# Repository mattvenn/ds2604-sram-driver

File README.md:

# pinball high scores

Reading the high scores out of the SRAM of a pinball machine.

[inspiration](http://spritesmods.com/?art=twitter1943)

[Tweet thread
documentation](https://threadreaderapp.com/thread/1040240733838557184.html)

After modelling, testing and reading/writing to the SRAM. I only needed to
listen to the bus lines to know when the data was being read. That is done by
[addr_listener](hdl/addr_listener):

    always @(clk) begin
        if(sram_ce) begin
            if(ce_counter < WAIT)
                ce_counter <= ce_counter + 1;
            else if(ce_counter == WAIT) begin
                case(sram_address)
                    sc_100_k:
                        high_score[23:20] <= sram_data_pins[3:0];
                    sc_10_k:
                        high_score[19:16] <= sram_data_pins[3:0];
                    sc_1_k:
                        high_score[15:12] <= sram_data_pins[3:0];
                    sc_100:
                        high_score[11: 8] <= sram_data_pins[3:0];
                    sc_10:
                        high_score[ 7: 4] <= sram_data_pins[3:0];
                    sc_1:
                        high_score[ 3: 0] <= sram_data_pins[3:0];
                endcase
            end
        else
            ce_counter <= 0;
        end 
    end

## plan

* the ds2064 is socketed, so make a [breakout board](ram-fpga) that passes through the connections. 
* add an FPGA that can listen to the 13 address lines, the 8 data lines and the 3 read/write/select pins = 24pins.
* when in write mode, with address in the high score range the FPGA reads the data off the bus.
* write [ds2064 driver](hdl/sram_driver/README.md)

## board test

* data pins tx - ok
* data pins rx - ok - very high impedance!
* addr pins tx - ok
* addr pins rx - ok
* ctrl pins rx - ok
* ctrl pins tx - ok
* on programming fpga, 5v line draws up to 40mA
* added 10k resistor from tranceiver !oe to FPGA 3.3v to keep them off while being programmed

## functional test

* read and write work separately with python control
* however, a write followed by a read works with ram non connected!

# Resources

http://www.pinballsupernova.com/Williams%20Repair%20Guide/Williams%201990-1999%20WPC.pdf
page 20 ram details

emulator https://github.com/neophob/wpc-emu
http://bcd.github.io/freewpc/The-WPC-Hardware.html#The-WPC-Hardware

The CPU board contains the main processor: a Motorola 68B09E, running at 2Mhz. It is an 8-bit/16-bit CPU with a 64KB address space. Bank switching is required to address more than 64KB. On reset, location 0xFFFE is read to determine the address of the first instruction.

8KB of RAM is located at physical address 0x0000. When power is turned off, three AA batteries on the CPU board maintain the state of the RAM. 

## WPC89

fairly sure this is the main board on my doctor who pinball.
[good overview here](http://level42.ca/files/PinRepair/System%20WPC/WPC%20part1/index1.htm)

It uses a battery backed up [ds2064](docs/ds2064.pdf) to store audits and score I hope.

[Schematic](docs/wpc89.pdf)

# Available machines to try

## bride

https://www.ipdb.org/machine.cgi?gid=1502
williams wpc

## high speed

https://www.ipdb.org/machine.cgi?id=1176
Williams System 11

## grand lizard

https://www.ipdb.org/machine.cgi?id=1070
williams system 11

## fire power 

https://www.ipdb.org/machine.cgi?id=856
williams system 6  (rottendog MPU327-4)
good photo: https://pinside.com/pinball/market/classifieds/archive/25465

rottendog sram chip:
https://www.mouser.es/datasheet/2/12/AS6C6264A-1288481.pdf

initial high score is 550,000 = 0x00_g08_64_70 

couldn't find it, so got a fake new score: 803950 = 0x0c_44_6e
         = 80 39 50

         = 50 39 50

motorola 6800 is big endian, intel is little endian

After searching for packed BCD of default string - got a match at 0x1149

    grep -A3 '^1149' dump.8192.5
    1149 55
    114a 00
    114b 00
    114c 00

Then checked for the new high score that we set 803950:

    grep -A3 '^1149' dump.8000.newhigh
    1149 80
    114a 03
    114b 39
    114c 05

Write this to a default chip:

    ./control.py --port /dev/ttyUSB1 --addr-start 1149 --addr-end 114d --read --hex
    1149 80
    114a 03
    114b 39
    114c 05

And then read it back:

    ./control.py --port /dev/ttyUSB1 --addr-start 1149 --addr-end  114d --read --hex
    1149 80
    114a 03
    114b 39
    114c 05

But display shows 503950! Checked one byte before start address 1148:

    55 00 00:
    1148 05
    1149 55
    114a 00
    114b 00
    114c 00

    80 39 50:
    1148 08
    1149 80
    114a 03
    114b 39
    114c 05

And can see it's the low nibble in each byte. Don't know what the upper nibble
represents. Wrote 10k to the score and it works, can beat it easily - which
should make the next step easier.

wrote 10k with:

    ./control.py --port /dev/ttyUSB1 --addr-start 1148 --addr-end  114d --write --hex --value 0001000000

only lower half of the byte

    1148 : 100ks
    1149 : 10ks
    114a : 1ks
    114b : 100's
    114c : 10's
    114d : 1's

so a write to 1149 is the 10k number.

## doctor who

https://www.ipdb.org/machine.cgi?id=738
williams wpc (fliptronics2)

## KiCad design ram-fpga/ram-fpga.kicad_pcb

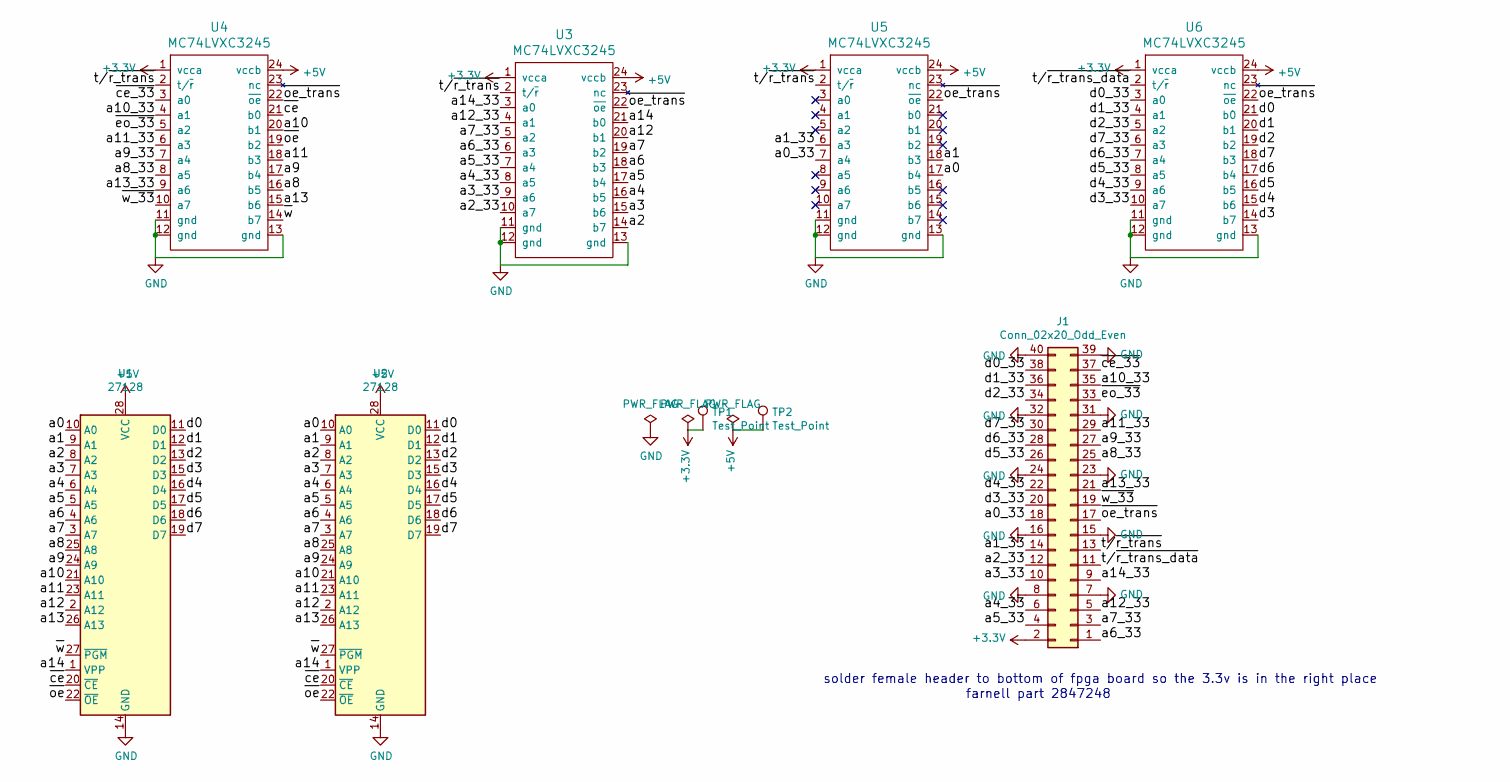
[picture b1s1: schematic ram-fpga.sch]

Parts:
J1: Conn_02x20_Odd_Even; PinHeader_2x20_P2.54mm_Vertical_SMD
TP1, TP2: Test_Point; Pin_D0.7mm_L6.5mm_W1.8mm_FlatFork
U1, U2: 27128; DIP-28_W15.24mm
U3, U4, U5, U6: MC74LVXC3245; SOIC-24W_7.5x15.4mm_P1.27mm; farnell # 2630416

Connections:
+3V3: J1.2, TP1.1, U3.1 (vcca), U4.1 (vcca), U5.1 (vcca), U6.1 (vcca)
+5V: TP2.1, U1.28 (VCC), U2.28 (VCC), U3.24 (vccb), U4.24 (vccb), U5.24 (vccb), U6.24 (vccb)
/a0: U1.10 (A0), U2.10 (A0), U5.17 (b4)
/a0_33: J1.18, U5.7 (a4)
/a1: U1.9 (A1), U2.9 (A1), U5.18 (b3)
/a1_33: J1.14, U5.6 (a3)
/a2: U1.8 (A2), U2.8 (A2), U3.14 (b7)
/a2_33: J1.12, U3.10 (a7)
/a3: U1.7 (A3), U2.7 (A3), U3.15 (b6)
/a3_33: J1.10, U3.9 (a6)
/a4: U1.6 (A4), U2.6 (A4), U3.16 (b5)
/a4_33: J1.6, U3.8 (a5)
/a5: U1.5 (A5), U2.5 (A5), U3.17 (b4)
/a5_33: J1.4, U3.7 (a4)
/a6: U1.4 (A6), U2.4 (A6), U3.18 (b3)
/a6_33: J1.1, U3.6 (a3)
/a7: U1.3 (A7), U2.3 (A7), U3.19 (b2)
/a7_33: J1.3, U3.5 (a2)
/a8: U1.25 (A8), U2.25 (A8), U4.16 (b5)
/a8_33: J1.25, U4.8 (a5)
/a9: U1.24 (A9), U2.24 (A9), U4.17 (b4)
/a9_33: J1.27, U4.7 (a4)
/a10: U1.21 (A10), U2.21 (A10), U4.20 (b1)
/a10_33: J1.35, U4.4 (a1)
/a11: U1.23 (A11), U2.23 (A11), U4.18 (b3)
/a11_33: J1.29, U4.6 (a3)
/a12: U1.2 (A12), U2.2 (A12), U3.20 (b1)
/a12_33: J1.5, U3.4 (a1)
/a13: U1.26 (A13), U2.26 (A13), U4.15 (b6)
/a13_33: J1.21, U4.9 (a6)
/a14: U1.1 (VPP), U2.1 (VPP), U3.21 (b0)
/a14_33: J1.9, U3.3 (a0)
/d0: U1.11 (D0), U2.11 (D0), U6.21 (b0)
/d0_33: J1.38, U6.3 (a0)
/d1: U1.12 (D1), U2.12 (D1), U6.20 (b1)
/d1_33: J1.36, U6.4 (a1)
/d2: U1.13 (D2), U2.13 (D2), U6.19 (b2)
/d2_33: J1.34, U6.5 (a2)
/d3: U1.15 (D3), U2.15 (D3), U6.14 (b7)
/d3_33: J1.20, U6.10 (a7)
/d4: U1.16 (D4), U2.16 (D4), U6.15 (b6)
/d4_33: J1.22, U6.9 (a6)
/d5: U1.17 (D5), U2.17 (D5), U6.16 (b5)
/d5_33: J1.26, U6.8 (a5)
/d6: U1.18 (D6), U2.18 (D6), U6.17 (b4)
/d6_33: J1.28, U6.7 (a4)
/d7: U1.19 (D7), U2.19 (D7), U6.18 (b3)
/d7_33: J1.30, U6.6 (a3)
/t/~r_trans: J1.13, U3.2 (t/~r), U4.2 (t/~r), U5.2 (t/~r)
/t/~r_trans_data: J1.11, U6.2 (t/~r)
/~ce: U1.20 (~CE), U2.20 (~CE), U4.21 (b0)
/~ce_33: J1.37, U4.3 (a0)
/~eo_33: J1.33, U4.5 (a2)
/~oe: U1.22 (~OE), U2.22 (~OE), U4.19 (b2)
/~oe_trans: J1.17, U3.22 (~oe), U4.22 (~oe), U5.22 (~oe), U6.22 (~oe)
/~w: U1.27 (~PGM), U2.27 (~PGM), U4.14 (b7)
/~w_33: J1.19, U4.10 (a7)
GND: J1.7, J1.8, J1.15, J1.16, J1.23, J1.24, J1.31, J1.32, J1.39, J1.40, U1.14 (GND), U2.14 (GND), U3.11 (gnd), U3.12 (gnd), U3.13 (gnd), U4.11 (gnd), U4.12 (gnd), U4.13 (gnd), U5.11 (gnd), U5.12 (gnd), U5.13 (gnd), U6.11 (gnd), U6.12 (gnd), U6.13 (gnd)

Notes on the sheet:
solder female header to bottom of fpga board so the 3.3v is in the right place
farnell part 2847248

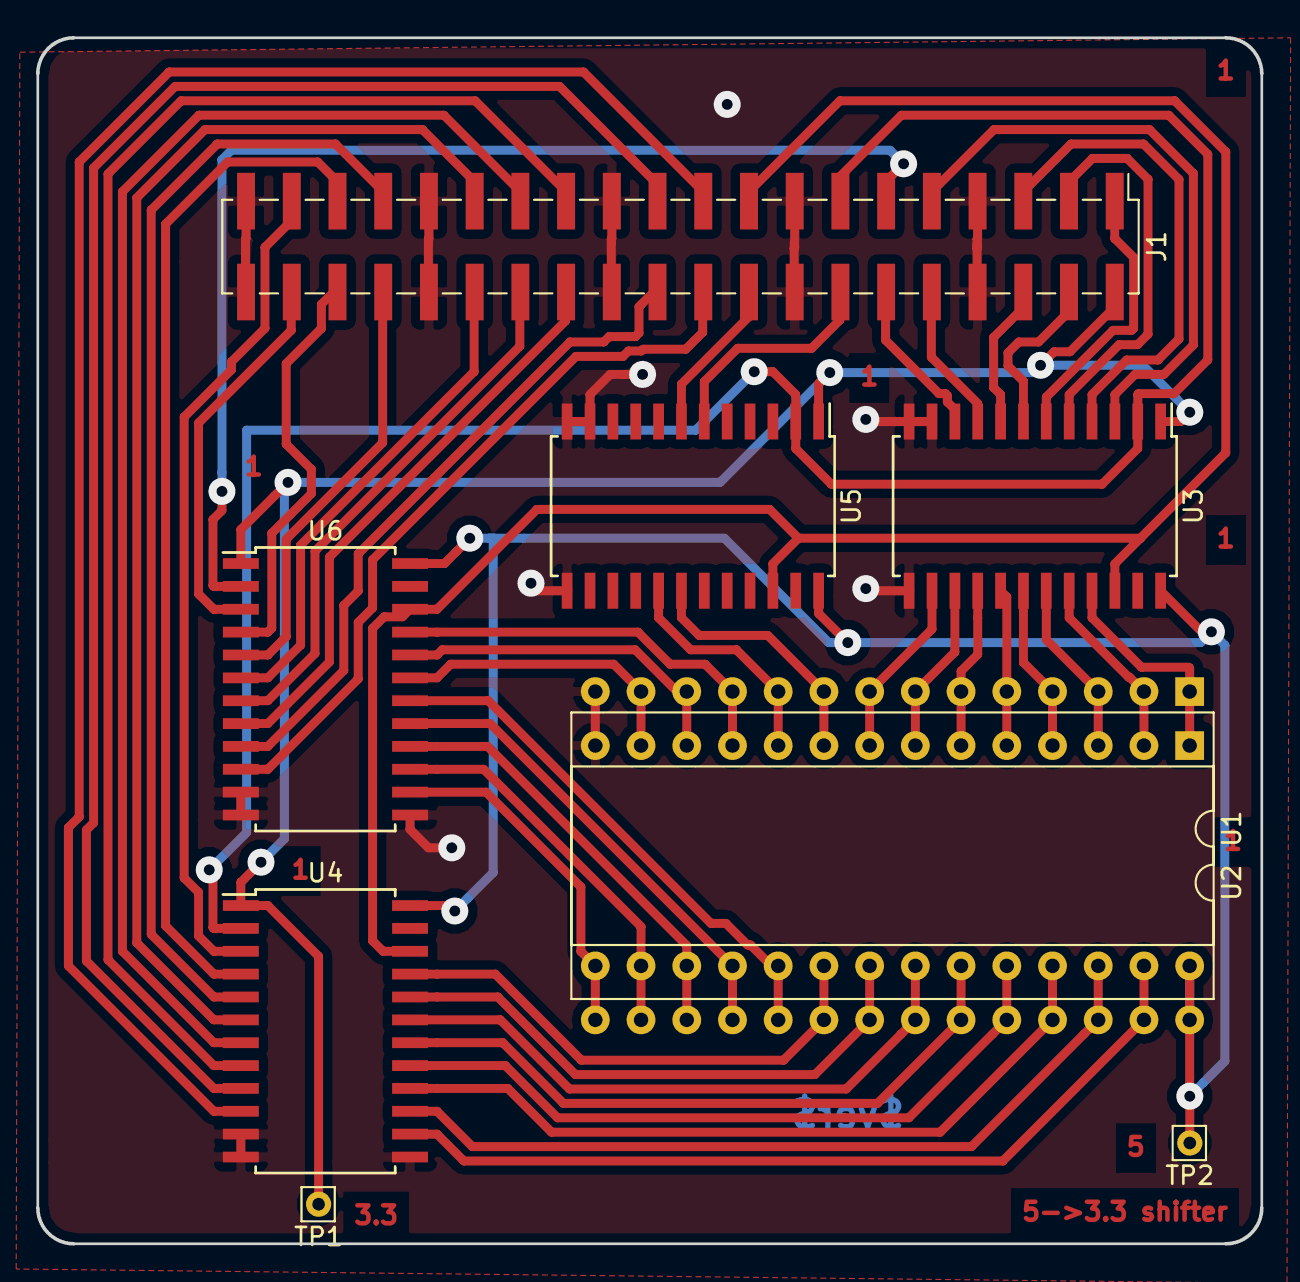
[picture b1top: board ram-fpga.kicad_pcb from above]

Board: 2 copper layers, 68.0 x 67.0 mm, 9 parts (0 on the bottom side), 58 nets.

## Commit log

2018-09-10 readme
2018-09-10 add pdfs
2018-09-10 ram32 pic
2018-09-11 switch to smt header
2018-09-11 top demo reads all addresses
2018-09-11 parameterise wait time properly
2018-09-11 reorg
2018-09-11 serial
2018-09-11 control via serial
2018-09-12 output test for addr and data
2018-09-12 ctrl pins tested
2018-09-12 missing file
2018-09-12 new sram datasheet
2018-09-12 simple read/write test with real RAM working
2018-09-12 random read/write test working with inout data pins
2018-09-12 print number
2018-09-12 readme and changed orientation of schematic
2018-09-12 schematic pdf & board png
2018-09-12 note about 10k pullup
2018-09-12 grouped pins by function
2018-09-13 fixed testbench after changing parameter
2018-09-13 command line args
2018-09-13 cli args
2018-09-13 iverilog search path
2018-09-13 start and end addresses
2018-09-13 use serial to control top
2018-09-13 state filters for gtkw
2018-09-13 remove default true, add exit condition
2018-09-13 appears to be working - need to check if still has data stuck bug
2018-09-13 remove a bit of print debugging
2018-09-14 notes on high score
2018-09-14 read mode board test
2018-09-14 a few of the sram pins needed reassignment for rottendog
2018-09-14 hex dump mode
2018-09-15 successfully read and write high score
2018-09-15 listens for address reads at the high score location and shows on leds
2018-09-15 add serial port to addr listener and serial command to control.py to read high score
2018-09-15 search for patterns in the dump file
2018-09-15 auto tweeter
2018-09-15 docs
